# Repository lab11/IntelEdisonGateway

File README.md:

# Intel Edison-based Gateway
<!--
A gateway design based on Intel Edison, which features two 802.15.4
radios, Ethernet controller, micro SD slot, built-in Wifi and BLE radios.

&nbsp;&nbsp;&nbsp;&nbsp;&nbsp;&nbsp;&nbsp;&nbsp;&nbsp;

-->
Second generation of Intel Edison Gateway. The gateway supports a wide range 
of radios / connectivity including 802.15.4, Wifi, BLE, Ethernet, LTE and GPS.
The precompiled linux kernel [image](https://github.com/lab11/IntelEdisonGateway/tree/master/kernel_patch/3.10.98/kernel_image) 
(based on Intel release, version 3.10.98) comes with necessary drivers for the
cellular modem and Ethernet controller.

The onboard cellular modem is [NimbeLink Skywire 4G LTE](http://nimbelink.com/skywire-cellular-modem-lte/),
which supports 100 Mb downlink and 50 Mb uplink and integrated GPS radio.
The cellular radio speaks Qualcomm MSM Interface (QMI), which allows the radio
to be mounted as a network adapter directly in Linux with [libqmi](https://www.freedesktop.org/wiki/Software/libqmi/).

The board is designed to fit in the off-the-shelf extruded aluminum enclosure 
[B2-080BK](http://www.boxenclosures.com/category/product_details.html?product__id=258909).

<!--
[LGSInnovations](https://github.com/LGSInnovations/Edison-Ethernet) has great
documentation of how to use LAN9512 on ubilinux.
The kernel module for smsc95xx (Ethernet controller) can be found [here](https://github.com/LGSInnovations/Edison-Ethernet/releases),
as well as the [installation guide](https://github.com/LGSInnovations/Edison-Ethernet/blob/master/guides/installation.md).

[edison_front]: https://github.com/lab11/IntelEdisonGateway/blob/master/images/edison_front.png "Front"

Pin Out
-------

Header on the left side of the PCB:

| Pin | Signal |   | Signal | Pin |
|-----|--------|---|--------|-----|
| 1   | MISO   |   | MOSI   | 2   |
| 3   | SCLK   |   | !CS1   | 4   |
| 5   | SDA    |   | SCL    | 6   |
| 7   | RX     |   | TX     | 8   |
| 9   | GP46   |   | GP45   | 10  |
| 11  | PA5    |   | GP44   | 12  |
| 13  | PA6    |   | PA3    | 14  |
| 15  | PA7    |   | PA4    | 16  |
| 17  | GND    |   | GND    | 18  |
-->

Pin Out
-------

Header on the left side of the PCB. This is changed from the previous version:

| Pin | Signal  |   | Signal  | Pin |
|-----|---------|---|---------|-----|
| 1   | VCC3.3  |   | VSYS3.9 | 2   |
| 3   | PA4     |   | PA5     | 4   |
| 5   | PA3     |   | GP46    | 6   |
| 7   | GND     |   | GND     | 8   |
| 9   | UART TX |   | UART RX | 10  |
| 11  | I2C SCL |   | I2C SDA | 12  |
| 13  | SPI CS1 |   | SPI CLK | 14  |
| 15  | MOSI    |   | MISO    | 16  |

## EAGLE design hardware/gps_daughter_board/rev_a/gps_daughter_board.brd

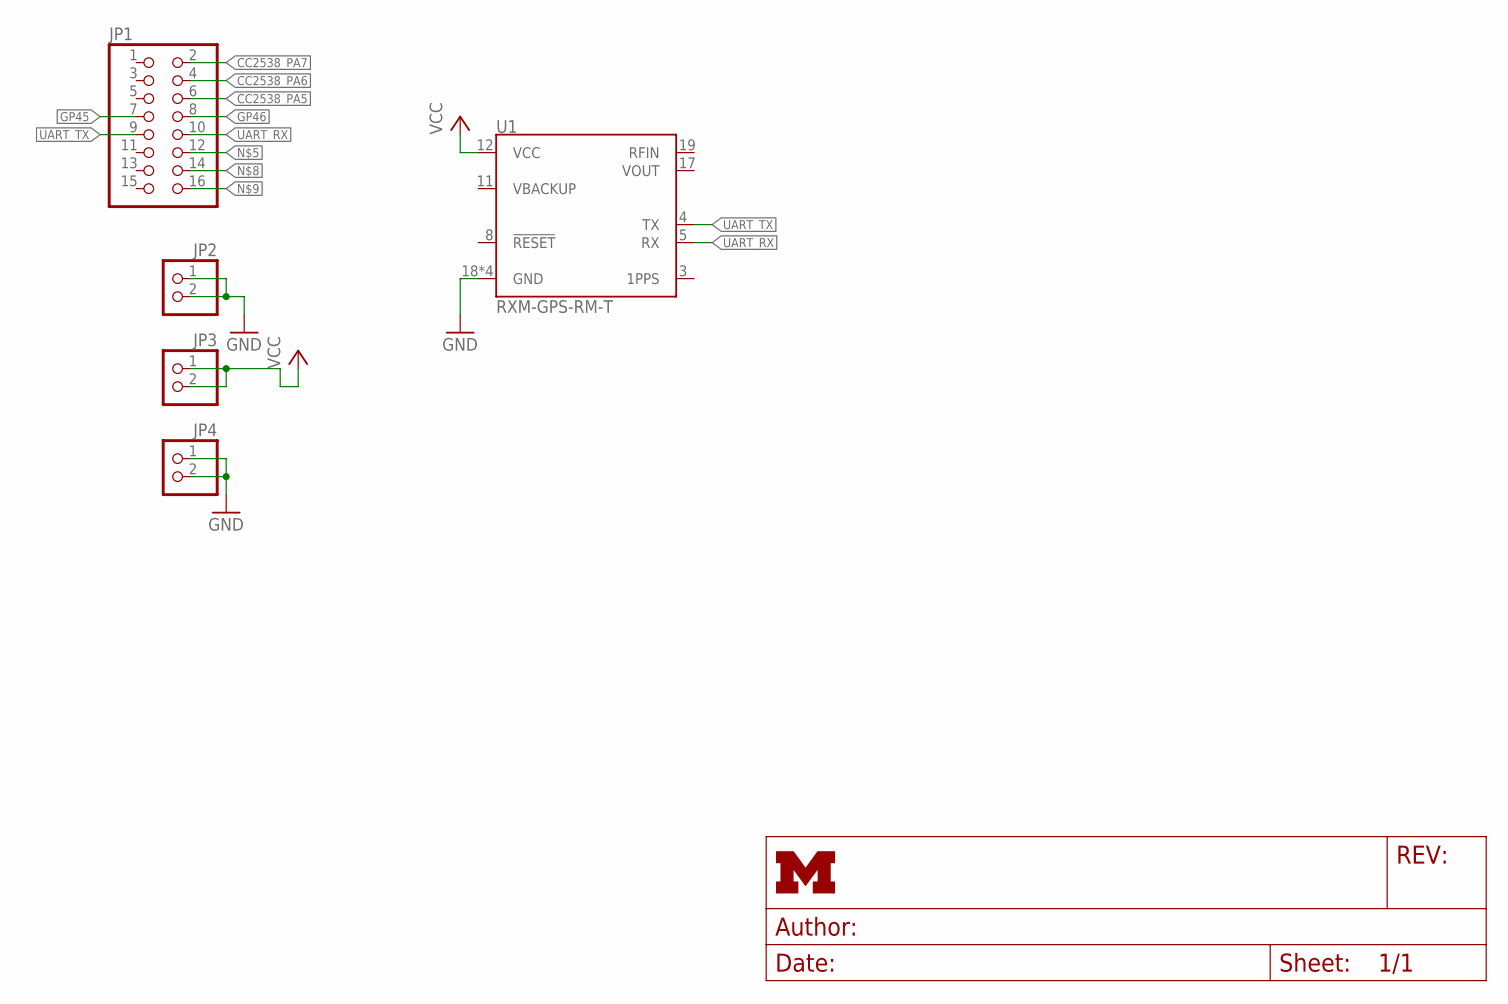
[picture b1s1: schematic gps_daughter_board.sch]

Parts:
JP1: PINHD-2X8; 2X08
JP2, JP3, JP4: PINHD-1X2; 1X02
U1: RXM-GPS-RM-T

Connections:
CC2538_PA5: JP1.6
CC2538_PA6: JP1.4
CC2538_PA7: JP1.2
GND: JP2.1, JP2.2, JP4.1, JP4.2, U1.18 (GND), U1.20 (GND), U1.21 (GND), U1.22 (GND)
GP45: JP1.7
GP46: JP1.8
UART_RX: JP1.10, U1.5 (RX)
UART_TX: JP1.9, U1.4 (TX)
VCC: JP3.1, JP3.2, U1.12 (VCC)

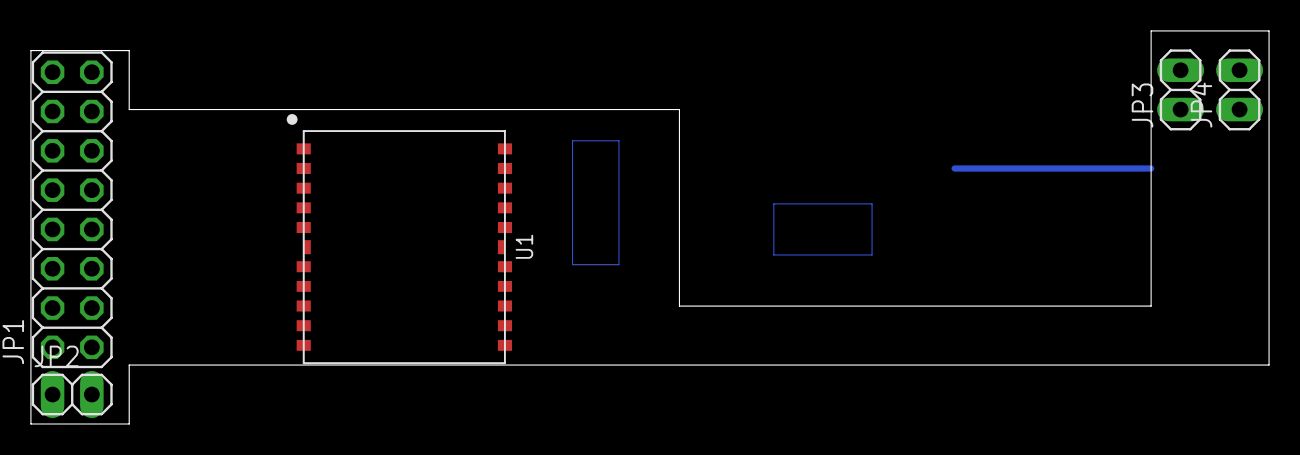
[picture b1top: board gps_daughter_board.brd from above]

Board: 2 copper layers, 80.0 x 25.4 mm, 5 parts (0 on the bottom side), 4 nets.

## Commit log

2016-01-18 commit hardware design files
2016-01-18 update readme message
2016-01-18 add pictures
2016-01-19 update schematic
2016-01-27 add some led control python scripts
2016-02-01 add yocto kernel patch hack to disable both chip select line in SPI
2016-02-04 add Triumvi receiver script
2016-02-04 add method post to GATD
2016-02-05 add mraa number to gpio number conversion
2016-02-09 fix key missing error
2016-02-10 working on publish triumvi data
    better handling threads
    publish to mqtt
2016-02-11 rename mqtt
2016-02-11 added systemd file
2016-02-11 updates for triumvi.py
    trying to figure out why it stops
2016-02-18 add length check, discard cruppted SPI packet
2016-02-18 add spi length check
2016-02-22 remove sleep(0.01) before sending another spi read instead, read GPIO state to determine if CC2538 is ready
    add a reset counter, once CC2538 keeps sending bogus data
    until certain point, reset it
2016-02-22 increase the spi rate to 2 MHz
2016-02-25 commit start to gps board
2016-02-27 add cc2538 radio on/off features
2016-03-02 clean up the outgoing triumvi packets
2016-03-03 add 60 second watchdog
2016-03-04 add cc2538 binary
2016-04-09 add cad files for case
    includes zortrax project files
2016-05-19 update 3d models for case
2016-05-20 add flash script
2016-06-07 add new case models and files
2016-06-17 add case designs
2016-06-25 super usage of build plate
2016-07-14 add case picture
2016-07-14 add pic
2016-07-19 change 'External voltage supply' to 'external voltage waveform'
2016-07-20 fix a missing comma
2016-07-21 remove LED debugging macro
2016-07-21 Add original patch file so difference can be found
2016-07-22 add triumvi scripts to support decoding PF, VRMS, IRMS This binary / script supports old triumvi (w/o PF... etc) but the old binary / script cannot decode the extended packet
2016-07-23 decode triumvi packets with 2 bytes PF, VRMS, IRMS
2016-07-23 supports 2 bytes PF, VRMS, IRMS
2016-07-24 decode ina gain
2016-07-27 add forwarding binary
2016-07-27 cleanup cc2538 forwarding binary
2016-07-27 mraa spi write will potentially stuck when the length is longer than 25-ish split two transactions
2016-07-30 add 802.15.4 raw packet parser add Triumvi AES decryption
2016-07-31 add triumvi formatter
2016-07-31 add frame type
2016-08-01 add pinout
2016-08-01 fix invalid address mode fix triumvi packet handling
2016-10-06 support APS3B12 control capability
2016-10-07 add aps3b12 triumvi handler
2016-10-07 change port to 4909
2016-10-07 fix floating point
2016-10-07 add SIGINT handler
2016-10-07 check state before sending command
2016-10-07 update state check
2016-10-07 fix a typo
2016-10-11 add debugging info
2016-10-11 add coefficient dump script
2016-10-11 revert the change
2016-10-13 add warning host to monitor non-linear increase load
2016-10-13 fix the warning code
2016-10-17 add aps3b12 control packet handling
2016-10-17 remove local aps3b12 handling
2016-10-17 remove unused files
2016-10-17 fix bug
2016-10-18 remove redudent connection
2016-10-18 fix exception handling
2016-10-18 revert to old version
2016-10-28 restructure edison kernel files
2016-10-28 move kernel config file to correct location
2016-10-28 add edison kernel driver modules
2016-10-28 add le910 macro
2016-10-28 add serial port comm to le910 cellular modem
2016-10-29 add more commands
2016-11-03 update le910_gps script
2016-11-03 remove swap file
2016-11-03 fix gps representation error
2016-11-08 add script to enable / disable network adapter on linux machine
2016-11-08 add qmi-network check
2016-11-08 update qmicli commands
2016-11-08 rename to offline gps
2016-11-08 fix comment
2016-11-10 use dhclient instead of udhcpc
2016-12-10 add cc2538 flashing script
2016-12-12 fix triumvi.py
2016-12-12 generalize the find tty script
2016-12-12 add find le910 device script
2016-12-12 add v3 hardware design files
2016-12-12 mv old design file to v2 folder
2017-01-05 add software rtc feature
2017-01-05 add script to parse rtc time stamp
2017-01-06 bug fix
2017-01-09 add readme in bin folder
2017-01-18 add the ability to respond timing infomation to triumvi nodes
2017-01-20 remove redundent TCP connection
2017-01-24 use try block to catch error when RTC failed
2017-02-03 fix corrupt packet decode
2017-02-10 add front and back plates
2017-03-09 update gateway fwd binary
2017-03-09 add reset fifo feature
2017-03-22 add linux shutdown script which turns off le910
2017-03-22 add calibration coefficient parser
2017-03-29 add le910 SMS script
2017-03-30 add AD5304 driver
2017-03-30 fix dac code
2017-03-30 update readme file
2017-03-30 add v3 image
2017-03-30 fix image link
2017-03-30 fix image placement
2017-03-30 crop image
2017-03-30 clean up sms send code
2017-03-31 add spi mode changing on the fly
2017-03-31 remove print message
2017-05-02 update current interface coefficients
2017-05-03 update formatter
2017-05-07 v2 is actually v3
2017-05-07 better names
2017-05-07 old changes to plates
2017-05-07 add v3 case build files
2017-05-10 update le910 script
    use variable consistently
2017-05-22 update packet formatter, expand VRMS to 10 bits
2017-05-25 add RSSI packet parser
2017-06-23 parse RSSI field
2017-06-23 add gateway front/back panel gerber / layout files
